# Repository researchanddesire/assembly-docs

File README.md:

# assembly-docs

This repository is the public, editable content mirror for [R+D Assembly](https://ohai.researchanddesire.com). Rendered page titles and section headings link to their exact source lines under `content/docs/`.

Contributions target `main`. Documentation syncs run main to main: when a
change to `content/` merges into `main`, the notifier wakes `rad-app` (the hub),
which imports it into `rad-app` `main` and merges the import automatically. The
live site deploys from there. `staging` is never synced; for documentation,
`main` always wins.

This repository's `content/` tree mirrors `rad-app/apps/docs-ohai/content/`,
including every language and asset. English product pages use `.en.mdx`;
navigation uses `meta.en.json`. The four hardware repositories
(`researchanddesire/OSSM`, `Open-Source-Chastity-Lockbox_LKBX`,
`Open-Source-Deepthroat-Trainer_DTT` and `Open-Source-Wireless-Remote_RADR`)
supply their English product pages from their own `assembly-docs/` folders on
`main`. When a page exists in both places, the most recently changed copy wins,
and the OSSM BOM always comes from that repository's `hardware/bom.csv`. The hub
never writes back to this repository or to the hardware repositories.

Every change to `main`, including deletions, reaches the live site within
minutes without further review.

The notifier needs the organization's `RAD_VERSION_CONTROL_APP_ID` variable and
`RAD_VERSION_CONTROL_PRIVATE_KEY` secret with access to rad-app.

## Historical MkDocs tooling (not the active synchronization pipeline)

The remaining sections document legacy tooling retained for reference. Do not
use it to regenerate the active `content/` tree or dispatch directly to hardware.

Aggregates each hardware product's `assembly-docs/` folder into a single
MkDocs Material site, following the same architecture as
[dev-docs](https://github.com/researchanddesire/dev-docs).

## How it works

- Each Ohai product repo opts in with the GitHub topic `ohai-assembly-docs` and
  keeps its assembly package in `assembly-docs/` at the repo root: markdown
  pages, an `assets/` folder of images, `site.yml` metadata, and a `nav.yml`
  (`site_name` + `nav`) describing page order.
- `scripts/assemble-docs.sh` discovers eligible product repos, shallow-clones
  them, stages each `assembly-docs/` package, and replaces `docs/{product}/`
  only after that product assembles successfully.
- `.github/workflows/deploy.yml` assembles, builds, and deploys to GitHub
  Pages on:
  - pushes to `main` touching `docs/**`, `mkdocs.yml`, or `scripts/**`
  - `repository_dispatch` events of type `assembly-docs-rebuild`, sent by each
    product repo's `trigger-assembly-docs.yml` workflow when its
    `assembly-docs/**`, BOM, PCB, or cable-source changes
  - manual `workflow_dispatch`

## Products

Products are discovered from non-archived `researchanddesire/*` repositories
with the `ohai-assembly-docs` topic and valid `assembly-docs/site.yml`
metadata. Template repos and repos with unreplaced placeholders are skipped.

Products whose repos don't yet have an `assembly-docs/` folder are skipped
with a warning at assemble time.

## Local development

```bash
pip install -r requirements.txt

# Assemble from local checkouts (skips cloning):
ASSEMBLE_LOCAL="$HOME/Github" ./scripts/assemble-docs.sh

mkdocs serve
```

Without `ASSEMBLE_LOCAL`, the script discovers topic-tagged repos through the
GitHub API and clones them: via a per-repo read-only deploy key when
`ASSEMBLE_SSH_DIR` contains one, via `ASSEMBLE_GITHUB_TOKEN` if set, otherwise
over anonymous HTTPS (sufficient once the repos are public at cutover).

## Secrets

While product repos are private, CI needs an `ASSEMBLE_GITHUB_TOKEN` secret with
read access to the product repos so discovery can see topic-tagged private
repos. Per-repo read-only deploy keys are still supported as a transition path.

Each product repo's `trigger-assembly-docs.yml` needs a `DOCS_DISPATCH_TOKEN`
secret — a fine-grained PAT (or org secret) with `contents: write` on this
repo, since the default `GITHUB_TOKEN` cannot send cross-repo dispatches.

## Bill of Materials rendering

Each product's `hardware/bom.csv` is rendered into a polished, colour-coded HTML
Bill of Materials and embedded in that product's assembly-docs `bom.md` page.
The rendered BOM belongs to the **assembly docs only** — never to developer
docs. (Developer docs may document this workflow, as here, but must not embed
the rendered BOM.)

### Where things live

| Thing                                              | Path                                                                    |
| -------------------------------------------------- | ----------------------------------------------------------------------- |
| BOM data (source of truth, per product repo)       | `hardware/bom.csv`                                                      |
| Renderer                                           | `scripts/render_bom.py`                                                 |
| Category code → label → colour map (single source) | `scripts/bom_categories.py`                                             |
| Chip / table structure + focus styles              | `docs/stylesheets/assembly.css`                                         |
| BOM page (per product repo, carries the markers)   | `assembly-docs/bom.md`                                                  |
| Generated block markers                            | `<!-- BEGIN GENERATED BOM -->` … `<!-- END GENERATED BOM -->`           |
| PCB page / KiCanvas viewer assembly                | `scripts/split_pcb_design_assets.py` + `scripts/insert_kicanvas_pcb.py` |
| Cable harness source files                         | Product repo `hardware/cables/`                                         |

The renderer is **read-only** on `hardware/bom.csv` and validates its header
against the canonical [BOM schema](https://dev.researchanddesire.com/meta/bom-standard/)
(`dev-docs`); it never changes the schema.

### How it runs

Rendering happens **at assemble time**, so the embedded block is never committed
per-product and can never go stale:

- `scripts/assemble-docs.sh` clones each product repo and, for each, renders
  `hardware/bom.csv` into the assembled `docs/{product}/bom.md` between the
  markers. Commit SHA (used for commit-pinned source links) and release status
  are auto-detected from the product checkout's git.
- Product assembly packages carry `pcb-overview.md` and `cable-harnesses.md`.
  Legacy `## PCB design assets` sections from BOM pages are still moved into the
  standalone PCB page during assembly for migration safety.
- If `hardware/pcb/` contains KiCad board files (`**/*.kicad_pcb`), assembly
  copies those board files into the assembled site, preserving their relative
  subfolders, and embeds KiCanvas viewer previews. Non-KiCad PCB sources get
  the standalone page without a KiCanvas render.
- If a product's `bom.md` has no markers, or its `bom.csv` is a header-only
  template, the page is left untouched.
- Cable harnesses are product-level BOM assemblies. Detailed child cable BOMs
  belong to Wireviz-generated artifacts such as `.bom.tsv`, linked from the
  assembly cable page.

A self-contained **Lockbox BOM demo** (`demo/lockbox/`) validates the workflow
end-to-end without depending on a cloned repo or fabricating real product data.
Disable it with `ASSEMBLE_BOM_DEMO=0`.

### Run it locally

```bash
pip install -r requirements.txt

# Render the demo BOM into the assembled site and preview:
ASSEMBLE_LOCAL="$HOME/Github" ./scripts/assemble-docs.sh
mkdocs serve

# Render a single product's BOM into a page directly (read-only on the CSV):
python3 scripts/render_bom.py \
  --bom path/to/hardware/bom.csv \
  --page path/to/assembly-docs/bom.md \
  --repo-url https://github.com/researchanddesire/Lockbox \
  --require-markers
```

### When CI runs

- The site rebuilds when a product repo's `assembly-docs/**`, BOM CSVs,
  `hardware/pcb/**`, or `hardware/cables/**` changes
  (`templates/trigger-assembly-docs.yml` →
  `repository_dispatch` → `deploy.yml`), and on pushes to this repo's
  `docs/**` / `mkdocs.yml` / `scripts/**`.
- On a tagged product release, `templates/generate-bom-release.yml` (a caller in
  the product repo) invokes the reusable `.github/workflows/bom-release.yml`
  here, which renders a standalone `bom.html` and publishes it as a GitHub
  Actions artifact + Release asset — unless the repo already commits a
  `bom.html`.

### Troubleshooting

- **Page didn't update:** confirm `assembly-docs/bom.md` has both markers and
  that `hardware/bom.csv` has data rows (a header-only template is skipped).
- **`BOM header does not match the canonical RAD BOM schema`:** the CSV header
  drifted; fix `hardware/bom.csv` to match the 12-column schema exactly. The
  renderer will not change the schema.

## Cutover

At OSS cutover, add the `ohai-assembly-docs` topic to the canonical public
product repos, remove it from superseded private forks, set `site_url` in
`mkdocs.yml` to `https://ohai.researchanddesire.com/`, and configure the custom
domain in the Pages settings.

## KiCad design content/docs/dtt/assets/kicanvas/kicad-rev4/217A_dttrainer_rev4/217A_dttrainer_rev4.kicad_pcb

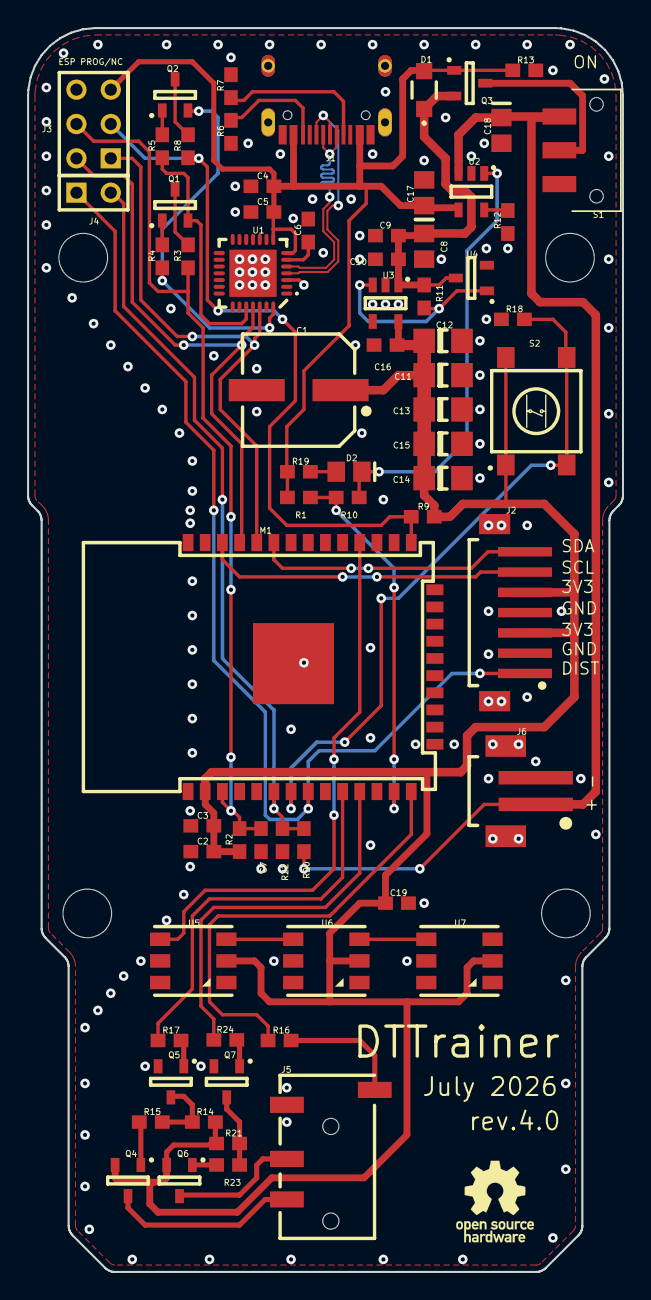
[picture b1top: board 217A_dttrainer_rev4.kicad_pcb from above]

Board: 2 copper layers, 44.0 x 92.0 mm, 78 parts (0 on the bottom side), 46 nets.

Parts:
@HOLE0, @HOLE1, @HOLE2, @HOLE3: (no value)
C1: 470uF/6.3V/NC; CAPAE-8.3x8.3h11.9
C2: 10uF; CAP_0603
C3, C5: 100nF; CAP_0603
C4, C9: 1uF; CAP_0603
C6: 100nF; CAP_0603_C6
C7: 10uF; CAP_0603_C7
C8: 10uF; CAP_0805
C10: 100nF; CAP_0603_C7
C11, C13, C14, C15: 100uF; CAP_1206
C12: 100uF; CAP_1206_C12
C16: 1uF; CAP_0603_C16
C17: 10uF; CAP_0805_C17
C18: 10uF; CAP_0805_C18
C19: 1uF; CAP_0603_C6
D1: B5819W; SOD-123F
D2: CHARGE; DIO_0805
J1: TYPE-C-31-M-12
J2: B7B-ZR; B7B-ZR-SM4-TF(LF)(SN)
J3: ESP PROG/NC; HDR-2x3
J4: ANA/NC; HDR-1x2
J5: 3.5mm Jack; Robu_3.5mm_jack
J6: LiPo; B2B-PH-K-S(LF)(SN)
Keepout_1: 1; ROUTE_KEEPOUT_1
Keepout_2: 2; ROUTE_KEEPOUT_2
Keepout_3: 3; ROUTE_KEEPOUT_3
Keepout_4: 4; ROUTE_KEEPOUT_4
Keepout_5: 5; ROUTE_KEEPOUT_5
Keepout_6: 6; ROUTE_KEEPOUT_6
M1: ESP32-WROOM-32D; ESP-WROOM-32
Q1, Q2: BC817; SOT23
Q3: Si2301; SOT23_Q3
Q4, Q6: MMBT4403; SOT23_Q4
Q5, Q7: BC817; SOT23_Q4
R1, R23: 1K; RES_0603
R2, R4, R5, R9, R14, R18: 10K; RES_0603_R2
R3, R8: 100R; RES_0603_R3
R6: 5.1K; RES_0603_R2
R7: 5.1K; RES_0603_R3
R10: 0R/NC; RES_0603_R10
R11: 10K; RES_0603_R10
R12: 2K; RES_0603_R2
R13, R21: 10K; RES_0603_R3
R15: 1K; RES_0603_R3
R16: 300R; RES_0603_R3
R17, R24: 1K; RES_0603_R2
R19: 2K; RES_0603_R3
R20: 100K; RES_0603_R20
R22: 100K; RES_0603_R22
S1: JS102011JAQN
S2: WAKE; B3S
U1: CP2102; QFN-28_5x5x0.5
U2: TP4054; SOT23-5
U3: ME6211C33; SOT23-5
U4: 3.3V Supervisor/NC; SOT23_U4
U5, U6, U7: WS2813

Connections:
CHG: D2.1, R10.2, U2.1
ESP_EN: C7.1, J3.4, M1.3, R2.2, R3.2
ESP_RXD: J3.1, M1.34, U1.26
ESP_TXD: J3.2, M1.35, U1.25
GND: C1.2, C2.2, C3.2, C4.2, C5.2, C6.2, C7.2, C8.2, C9.2, C10.2, C11.2, C12.2, C13.2, C14.2, C15.2, C16.2, C17.2, C18.2, C19.2, J1.A1B12, J1.B1A12, J1.GND1, J1.GND2, J1.GND3, J1.GND4, J2.2, J2.4, J2.8, J2.9, J3.6, J5.2, J6.2, J6.3, J6.4, M1.1, M1.15, M1.38, M1.39, Q5.2, Q7.2, R6.1, R7.1, R12.1, R13.1, R18.1, R22.1, U1.3, U1.29, U2.2, U3.2, U4.2, U5.5, U6.5, U7.5
IO0: J3.3, M1.25, R8.2, R9.1
IO12: M1.14, R16.2
IO14: M1.13, R1.1, R10.1
IO17: M1.28, U5.4
IO21: J2.7, M1.33
IO22: J2.6, M1.36
IO25: M1.10, R17.1
IO26: M1.11, R24.1
IO32: J2.1, J4.1, M1.8
IO34: J4.2, M1.6, R20.1, R22.2
IO35: M1.7, R18.2, S2.3, S2.4
Net_0: R12.2, U2.5
Net_1: Q5.3, R14.1, R15.1
Net_2: Q4.1, R15.2
Net_3: J5.4, Q4.3
Net_4: Q6.1, R23.2
Net_5: Q3.3, S1.2
Net_6: Q1.1, R4.2
Net_12: C6.1, U1.6
Net_23: Q2.1, R5.2
Net_25: Q1.2, R5.1, U1.24
Net_26: Q2.2, R4.1, U1.28
Net_29: R11.1, U3.3, U4.1
Net_30: Q7.3, R21.1, R23.1
Net_34: U5.3, U6.4
Net_35: U6.3, U7.4
Net_37: D2.2, R19.1
Net_43: Q5.1, R17.2
Net_44: Q7.1, R24.2
Net_45: J5.3, Q6.3
Net_47: J5.1, R16.1
Net_74: J1.B5, R6.2
Net_75: J1.A5, R7.2
Net_76: Q2.3, R8.1
Net_77: Q1.3, R3.1
USB_D_N: J1.A7, J1.B7, U1.5
USB_D_P: J1.A6, J1.B6, U1.4
VBAT: C18.1, J6.1, R20.2, S1.3, U2.3
VDD_3V3: C1.1, C2.1, C3.1, C11.1, C12.1, C13.1, C14.1, C15.1, C16.1, C19.1, J2.3, J2.5, M1.2, Q4.2, Q6.2, R2.1, R9.2, R14.2, R21.2, S2.1, S2.2, U3.5, U5.2, U6.2, U7.2
VDD_5V0: C8.1, C9.1, C10.1, D1.1, Q3.2, R11.2, U3.1, U4.3
VDD_USB: C4.1, C5.1, C17.1, D1.2, J1.A4B9, J1.B4A9, J3.5, Q3.1, R1.2, R13.2, R19.2, U1.7, U1.8, U2.4

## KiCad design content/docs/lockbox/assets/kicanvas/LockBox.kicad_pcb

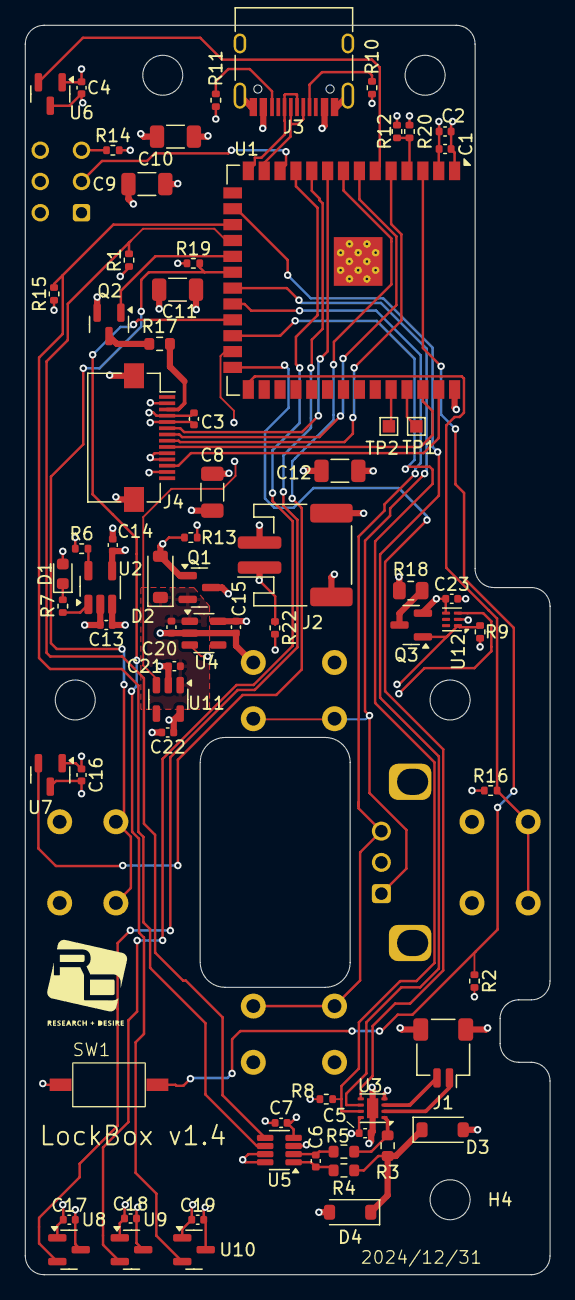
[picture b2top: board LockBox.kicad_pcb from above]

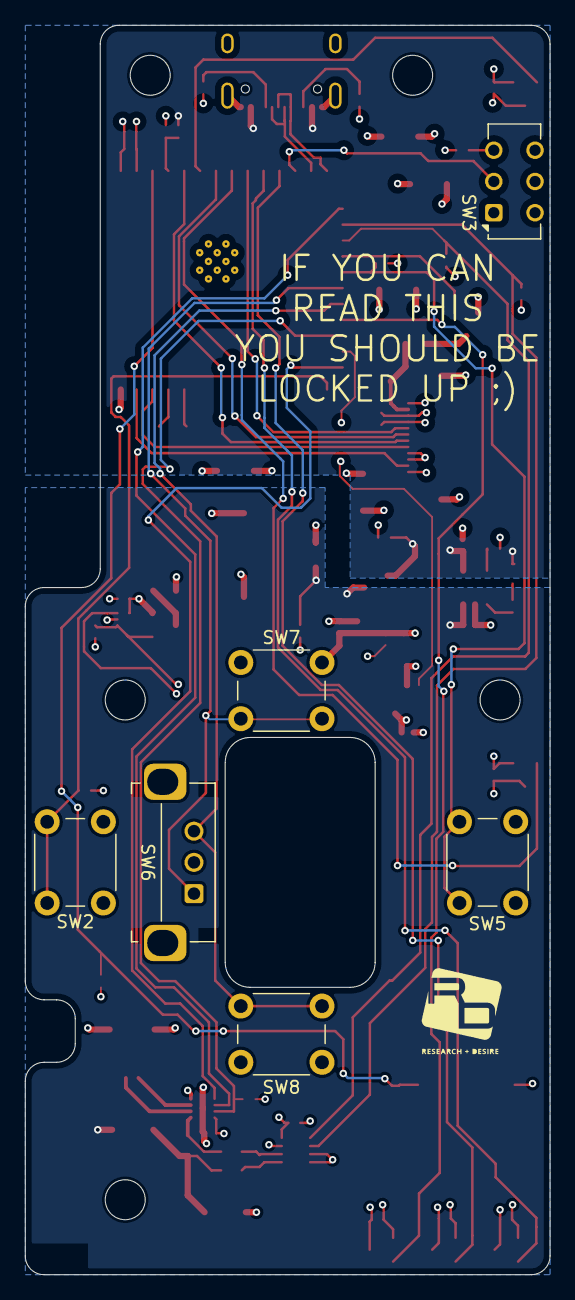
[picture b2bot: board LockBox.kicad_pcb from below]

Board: 4 copper layers, 42.0 x 100.0 mm, 81 parts (6 on the bottom side), 50 nets.

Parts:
C1, C4, C5, C6, C7, C16, C17, C18, C19, C23: 0.1u; C_0402_1005Metric
C2, C13, C14: 10u; C_0402_1005Metric
C3, C15, C20, C21, C22: 1u; C_0402_1005Metric
C8, C9, C10, C11, C12: 100u; C_1206_3216Metric
D1: LED_Small; LED_0603_1608Metric
D2, D3, D4: B5819W; D_SOD-123
H1, H2, H3, H4, H5: MountingHole; MountingHole_3.2mm_M3
J1: JST_SH_SM02B-SRSS-TB_1x02-1MP_P1.00mm_Horizontal
J2: S2B-PH-SM4-TB(LF)(SN); JST_PH_S2B-PH-SM4-TB_1x02-1MP_P2.00mm_Horizontal
J3: USB_C_Receptacle_USB2.0_16P; USB_C_Receptacle_HRO_TYPE-C-31-M-12
J4: AFC01-S14FCA-00; JUSHUO_AFC01-S14FCA-00
Q1: Si2301; SOT-23
Q2: AO3400; SOT-23
Q3: Q_PMOS_DGS; SOT-23
R1, R6, R7, R15: 2k; R_0402_1005Metric
R2, R8, R9, R13, R14, R16, R19, R22: 10k; R_0402_1005Metric
R3: 0.1; R_0603_1608Metric
R4, R5, R17: 10; R_0603_1608Metric
R10, R11: 5.1k; R_0402_1005Metric
R12, R20: 100k; R_0402_1005Metric
R18: 33; R_0805_2012Metric
SW1: SW_Push; SW_SPST_TSB008A2518A
SW2, SW5, SW7, SW8: SW_Push; SW_PUSH_6mm_H8mm
SW3: SW_SPDT; SW_CK_JS202011AQN_DPDT_Angled
SW6: PEC12R-2120F-N0012; RotaryEncoder_Bourns_Horizontal_PEC12R-2x17F-Nxxxx
TP1, TP2: TestPoint; TestPoint_Pad_1.0x1.0mm
U1: ESP32-S3-WROOM-1; ESP32-S3-WROOM-1-FIXED
U2: TP4054; SOT-23-5_HandSoldering
U3: DRV8210DSGR; WSON-8-1EP_2x2mm_P0.5mm_EP0.9x1.6mm
U4, U11: ME6211C33M5; SOT-23-5
U5: INA219AIDCN; SOT-23-8
U6, U7: TCS40DPR,LF; SOT-23
U8, U9, U10: TMR2101SO; SOT-23
U12: ST6519; ST_UDFN-6_1.0x1.45mm_P0.5mm

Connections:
+3V3: C1.1, C2.1, C5.1, C8.1, C9.1, C10.1, C11.1, C12.1, C15.1, C23.1, D4.2 (A), Q3.2 (S), R2.1, R9.1, R16.1, R19.1, U1.2 (3V3), U3.8 (VCC), U4.5 (V_{OUT}), U12.4 (VDD)
+5V: C14.1, D1.2 (A), D2.2 (A), J3.A4 (VBUS), J3.A9 (VBUS), J3.B4 (VBUS), J3.B9 (VBUS), Q1.1 (G), R12.1, R13.1, U2.4 (VCC)
+BATT: C13.1, D3.2 (A), J2.1, Q1.3 (D), R22.1, U2.3 (BAT)
/5V_DETECT: R12.2, R20.1, U1.4 (IO4)
/ACCY_EN: U1.25 (IO48), U11.3 (CE)
/BL_PWM: Q2.1 (G), U1.19 (IO11)
/HALL_OUT_1: U1.6 (IO6), U6.2 (OUT)
/HALL_OUT_2: U1.8 (IO15), U7.2 (OUT)
/LCD_A0: J4.7, U1.7 (IO7)
/LCD_SCK: J4.9, U1.38 (IO2)
/LCD_SDA: J4.8, U1.5 (IO5)
/MCU_and_UI/ENC_A: SW6.A, SW7.2, U1.21 (IO13)
/MCU_and_UI/ENC_B: SW6.B, SW8.2, U1.22 (IO14)
/MCU_and_UI/ESP_EN: R2.2, SW1.2, U1.3 (EN)
/MCU_and_UI/POWER_DETECT: SW3.2 (B), U1.12 (IO8)
/MCU_and_UI/USB_D+: J3.A6 (D+), J3.B6 (D+), U1.14 (IO20)
/MCU_and_UI/USB_D-: J3.A7 (D-), J3.B7 (D-), U1.13 (IO19)
/MCU_and_UI/USER_BACK: R16.2, SW2.2, U1.27 (IO0)
/MCU_and_UI/USER_ENTER: R19.2, SW5.2, U1.20 (IO12), U12.3 (~SR)
/MODE: R8.1, U1.24 (IO47), U3.7 (MODE)
/MTR1: U1.16 (IO46), U3.6 (IN1)
/MTR2: U1.26 (IO45), U3.5 (IN2)
/PWR_EN: Q3.1 (G), R9.2, R22.2, U4.3 (CE), U12.1 (~RST)
/SCL: R1.2, U1.18 (IO10), U5.5 (SCL)
/SDA: R15.2, U1.17 (IO9), U5.6 (SDA)
/Screen/LED-: J4.3, R17.1
/TMR_OUT_1: U1.10 (IO17), U8.2 (OUT)
/TMR_OUT_2: U1.11 (IO18), U9.2 (OUT)
/TMR_OUT_3: U1.23 (IO21), U10.2 (OUT)
/~LCD_CS: J4.12, U1.39 (IO1)
/~LCD_RES: J4.6, U1.9 (IO16)
GND: C1.2, C2.2, C3.2, C4.2, C5.2, C7.2, C8.2, C9.2, C10.2, C11.2, C12.2, C13.2, C14.2, C15.2, C16.2, C17.2, C18.2, C19.2, C20.2, C21.2, C22.2, C23.2, J1.MP (MountPin), J2.2, J2.MP (MountPin), J3.A1 (GND), J3.A12 (GND), J3.B1 (GND), J3.B12 (GND), J3.S1 (SHIELD), J4.2, J4.5, J4.13, J4.MP (MountPin), Q2.2 (S), R6.2, R8.2, R10.2, R11.2, R13.2, R14.2, R18.2, R20.2, SW1.1, SW2.1, SW5.1, SW6.C, SW6.SH, SW7.1, SW8.1, U1.1 (GND), U1.40 (GND), U1.41 (GND), U2.2 (GND), U3.4 (GND), U3.9 (PAD), U4.2 (V_{SS}), U5.3 (GND), U5.7 (A0), U5.8 (A1), U6.3 (GND), U7.3 (GND), U8.3 (GND), U9.3 (GND), U10.3 (GND), U11.2 (V_{SS}), U12.2 (VSS)
unnamed: D1.1 (K), R7.1
unnamed: C20.1, C21.1, D2.1 (K), Q1.2 (S), U4.1 (V_{IN}), U11.1 (V_{IN})
unnamed: D3.1 (K), D4.1 (K), R3.2, R4.1
unnamed: J1.1, U3.2 (OUT1)
unnamed: J1.2, U3.3 (OUT2)
unnamed: J3.A5 (CC1), R10.1
unnamed: J3.B5 (CC2), R11.1
unnamed: Q2.3 (D), R17.2
unnamed: Q3.3 (D), R18.1
unnamed: R14.1, SW3.3 (C)
unnamed: TP2.1, U1.36 (RXD0)
unnamed: TP1.1, U1.37 (TXD0)
unnamed: R6.1, U2.5 (PROG)
unnamed: R7.2, U2.1 (/CHRG)
unnamed: R3.1, R5.1, U3.1 (VM)
unnamed: C6.1, R4.2, U5.1 (IN+)
unnamed: C6.2, R5.2, U5.2 (IN-)
VDD: C3.1, C4.1, C7.1, C16.1, C17.1, C18.1, C19.1, C22.1, J4.4, J4.10, J4.11, R1.1, R15.1, U5.4 (VS), U6.1 (VCC), U7.1 (VCC), U8.1 (VCC), U9.1 (VCC), U10.1 (VCC), U11.5 (V_{OUT})

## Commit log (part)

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2026-06-13 Add RADR assembly docs support
2026-06-13 Commit assembled assembly docs content
2026-06-13 Skip unavailable assembly source repos
2026-06-13 Skip unavailable assembly source repos
    Skip product repos that cannot be cloned so an unavailable source does not block the assembly-docs Pages deploy.
2026-06-15 Target PCB overview page for KiCanvas
2026-06-16 Render nested KiCad boards in KiCanvas
2026-06-16 Discover Ohai assembly docs products
2026-06-16 Guard private Ohai discovery without token
2026-06-22 Match assembly docs to RAD styling
